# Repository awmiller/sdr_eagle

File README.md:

# sdr_eagle
various designs for different stages of development and manufacturers.

## Clone into the "eagle" directory created by the Eagle CAD installer

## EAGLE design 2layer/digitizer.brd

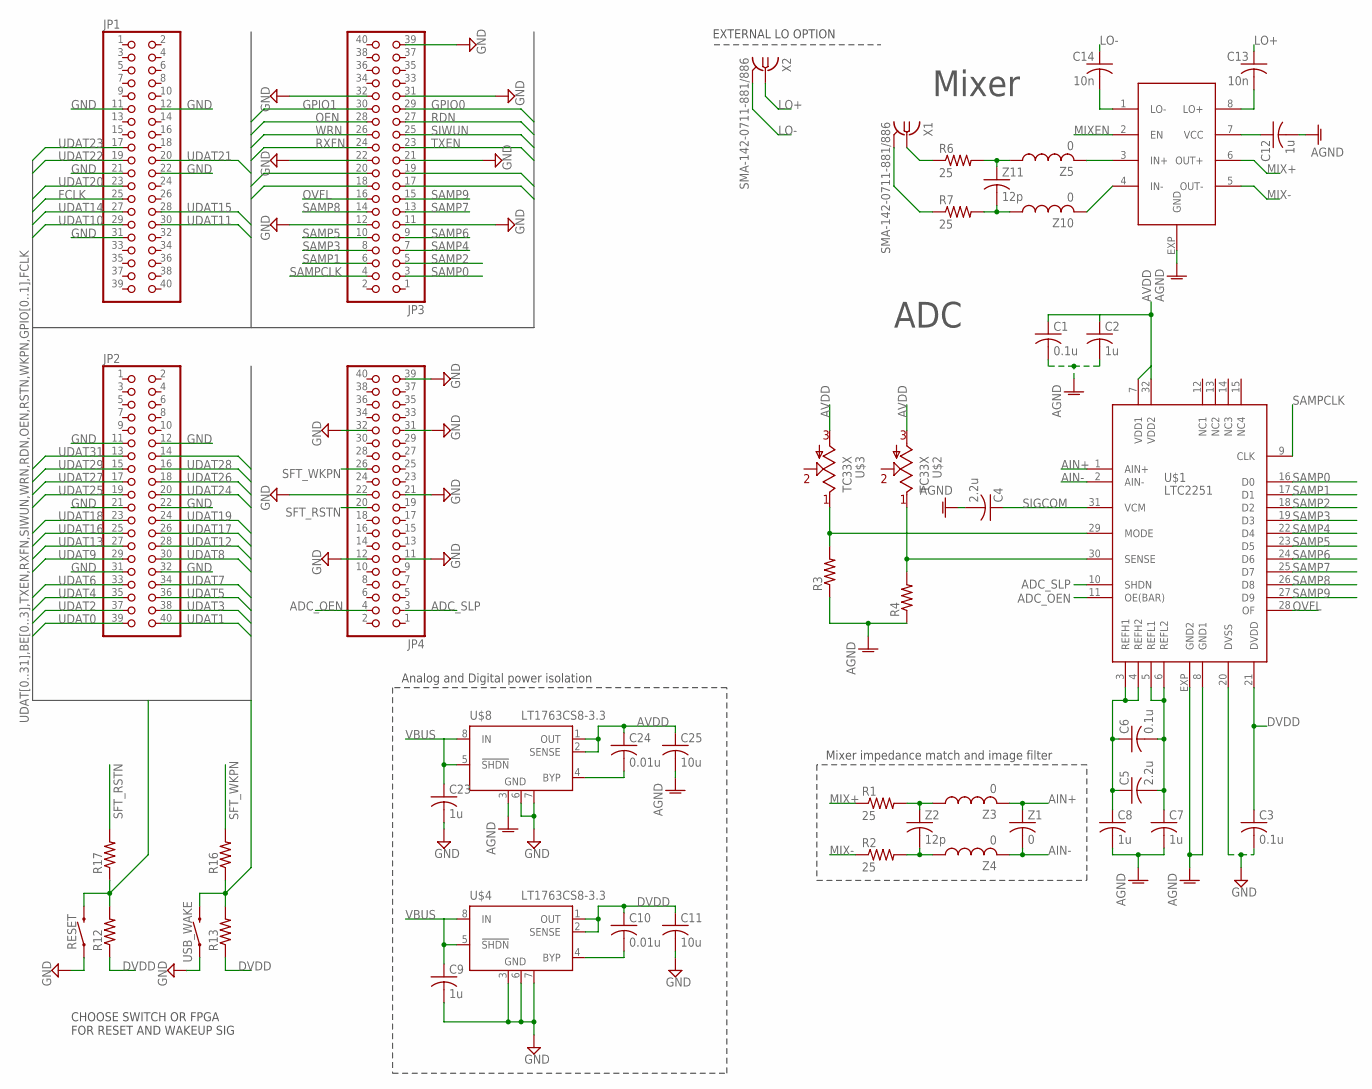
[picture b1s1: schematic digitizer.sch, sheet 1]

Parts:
C1, C3, C6: 0.1u; C0402
C2, C7, C8, C9, C12, C23: 1u; C0402
C4, C5: 2.2u; C0402
C10, C24: 0.01u; C0402
C11, C25: 10u; C0402
C13, C14: 10n; C0402
JP1, JP2, JP3, JP4: PINHD-2X20; 2X20
R1, R2, R6, R7: 25; R0402
R3, R4, R12, R13, R16, R17: R-US_R0402; R0402
RESET: MOMENTARY-SWITCH-SPST-SMD-6.0X3.5MM; TACTILE_SWITCH_SMD_6.0X3.5MM
U$1: LTC2251; HVQFN32
U$2, U$3: TC33X; SC59-POT
U$4, U$8: LT1763CS8-3.3; SOIC8
U$5: LT5560; DFN8-3X3
USB_WAKE: MOMENTARY-SWITCH-SPST-SMD-6.0X3.5MM; TACTILE_SWITCH_SMD_6.0X3.5MM
X1, X2: SMA-142-0711-881/886; J502-ND-142-0711-881/886
Z1: 0; C0402
Z2, Z11: 12p; C0402
Z3, Z4, Z5, Z10: 0; R0402

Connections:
ADC_OEN: JP4.4, U$1.11 (OE(BAR))
ADC_SLP: JP4.3, U$1.10 (SHDN)
AGND: C1.2, C2.2, C4.2, C7.2, C8.2, C12.2, C25.2, R3.1, R4.1, U$1.8 (GND1), U$1.EXP (GND2), U$5.EXP (GND), U$8.3 (GND)
AIN+: U$1.1 (AIN+), Z1.1, Z3.2
AIN-: U$1.2 (AIN-), Z1.2, Z4.2
AVDD: C1.1, C2.1, C24.1, C25.1, U$1.7 (VDD1), U$1.32 (VDD2), U$2.3, U$3.3, U$8.1 (OUT), U$8.2 (SENSE)
BE0: JP3.18; also elsewhere on the board
BE1: JP3.17; also elsewhere on the board
BE2: JP3.20; also elsewhere on the board
BE3: JP3.19; also elsewhere on the board
DVDD: C3.1, C10.1, C11.1, R12.1, R13.1, U$1.21 (DVDD), U$4.1 (OUT), U$4.2 (SENSE); also elsewhere on the board
FCLK: JP1.25; also elsewhere on the board
GND: C3.2, C9.2, C11.2, C23.2, JP1.11, JP1.12, JP1.21, JP1.22, JP1.31, JP2.11, JP2.12, JP2.21, JP2.22, JP2.31, JP2.32, JP3.11, JP3.12, JP3.21, JP3.22, JP3.31, JP3.32, JP3.39, JP4.11, JP4.12, JP4.21, JP4.22, JP4.31, JP4.32, RESET.1, U$1.20 (DVSS), U$4.3 (GND), U$4.6 (GND), U$4.7 (GND), U$8.6 (GND), U$8.7 (GND), USB_WAKE.1; also elsewhere on the board
GPIO0: JP3.29; also elsewhere on the board
GPIO1: JP3.30; also elsewhere on the board
LO+: C13.1, X2.1
LO-: C14.1, X2.G@1 (2), X2.G@2 (2), X2.G@3 (2), X2.G@4 (2)
MIX+: R1.1, U$5.6 (OUT+)
MIX-: R2.1, U$5.5 (OUT-)
MIXEN: U$5.2 (EN)
unnamed: R7.1, X1.G@1 (2), X1.G@2 (2), X1.G@3 (2), X1.G@4 (2)
unnamed: C5.1, C6.1, C8.1, U$1.3 (REFH1), U$1.4 (REFH2)
unnamed: C5.2, C6.2, C7.1, U$1.5 (REFL1), U$1.6 (REFL2)
unnamed: R3.2, U$1.29 (MODE), U$3.1
unnamed: R4.2, U$1.30 (SENSE), U$2.1
unnamed: R1.2, Z2.1, Z3.1
unnamed: R2.2, Z2.2, Z4.1
unnamed: C10.2, U$4.4 (BYP)
unnamed: R6.1, X1.1
unnamed: C24.2, U$8.4 (BYP)
unnamed: C12.1, U$5.7 (VCC)
unnamed: C14.2, U$5.1 (LO-)
unnamed: C13.2, U$5.8 (LO+)
unnamed: R6.2, Z5.1, Z11.1
unnamed: U$5.3 (IN+), Z5.2
unnamed: U$5.4 (IN-), Z10.2
unnamed: R7.2, Z10.1, Z11.2
OEN: JP3.28; also elsewhere on the board
OVFL: JP3.16, U$1.28 (OF)
RDN: JP3.27; also elsewhere on the board
RSTN: R12.2, R17.1, RESET.2; also elsewhere on the board
RXFN: JP3.24; also elsewhere on the board
SAMP0: JP3.3, U$1.16 (D0)
SAMP1: JP3.6, U$1.17 (D1)
SAMP2: JP3.5, U$1.18 (D2)
SAMP3: JP3.8, U$1.19 (D3)
SAMP4: JP3.7, U$1.22 (D4)
SAMP5: JP3.10, U$1.23 (D5)
SAMP6: JP3.9, U$1.24 (D6)
SAMP7: JP3.13, U$1.25 (D7)
SAMP8: JP3.14, U$1.26 (D8)
SAMP9: JP3.15, U$1.27 (D9)
SAMPCLK: JP3.4, U$1.9 (CLK)
SFT_RSTN: JP4.20, R17.2
SFT_WKPN: JP4.26, R16.2
SIGCOM: C4.1, U$1.31 (VCM)
SIWUN: JP3.25; also elsewhere on the board
TXEN: JP3.23; also elsewhere on the board
UDAT0: JP2.39; also elsewhere on the board
UDAT1: JP2.40; also elsewhere on the board
UDAT2: JP2.37; also elsewhere on the board
UDAT3: JP2.38; also elsewhere on the board
UDAT4: JP2.35; also elsewhere on the board
UDAT5: JP2.36; also elsewhere on the board
UDAT6: JP2.33; also elsewhere on the board
UDAT7: JP2.34; also elsewhere on the board
UDAT8: JP2.30; also elsewhere on the board
UDAT9: JP2.29; also elsewhere on the board
UDAT10: JP1.29; also elsewhere on the board
UDAT11: JP1.30; also elsewhere on the board
UDAT12: JP2.28; also elsewhere on the board
UDAT13: JP2.27; also elsewhere on the board
UDAT14: JP1.27; also elsewhere on the board
UDAT15: JP1.28; also elsewhere on the board
UDAT16: JP2.25; also elsewhere on the board
UDAT17: JP2.26; also elsewhere on the board
UDAT18: JP2.23; also elsewhere on the board
UDAT19: JP2.24; also elsewhere on the board
UDAT20: JP1.23; also elsewhere on the board
UDAT21: JP1.20; also elsewhere on the board
UDAT22: JP1.19; also elsewhere on the board
UDAT23: JP1.17; also elsewhere on the board
UDAT24: JP2.20; also elsewhere on the board
UDAT25: JP2.19; also elsewhere on the board
UDAT26: JP2.18; also elsewhere on the board
UDAT27: JP2.17; also elsewhere on the board
UDAT28: JP2.16; also elsewhere on the board
UDAT29: JP2.15; also elsewhere on the board
UDAT30: JP2.14; also elsewhere on the board
UDAT31: JP2.13; also elsewhere on the board
VBUS: C9.1, C23.1, U$4.5 (!SHDN), U$4.8 (IN), U$8.5 (!SHDN), U$8.8 (IN); also elsewhere on the board
WKPN: R13.2, R16.1, USB_WAKE.2; also elsewhere on the board
WRN: JP3.26; also elsewhere on the board

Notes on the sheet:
Mixer impedance match and image filter
Analog and Digital power isolation
Mixer
ADC
EXTERNAL LO OPTION
CHOOSE SWITCH OR FPGA FOR RESET AND WAKEUP SIG

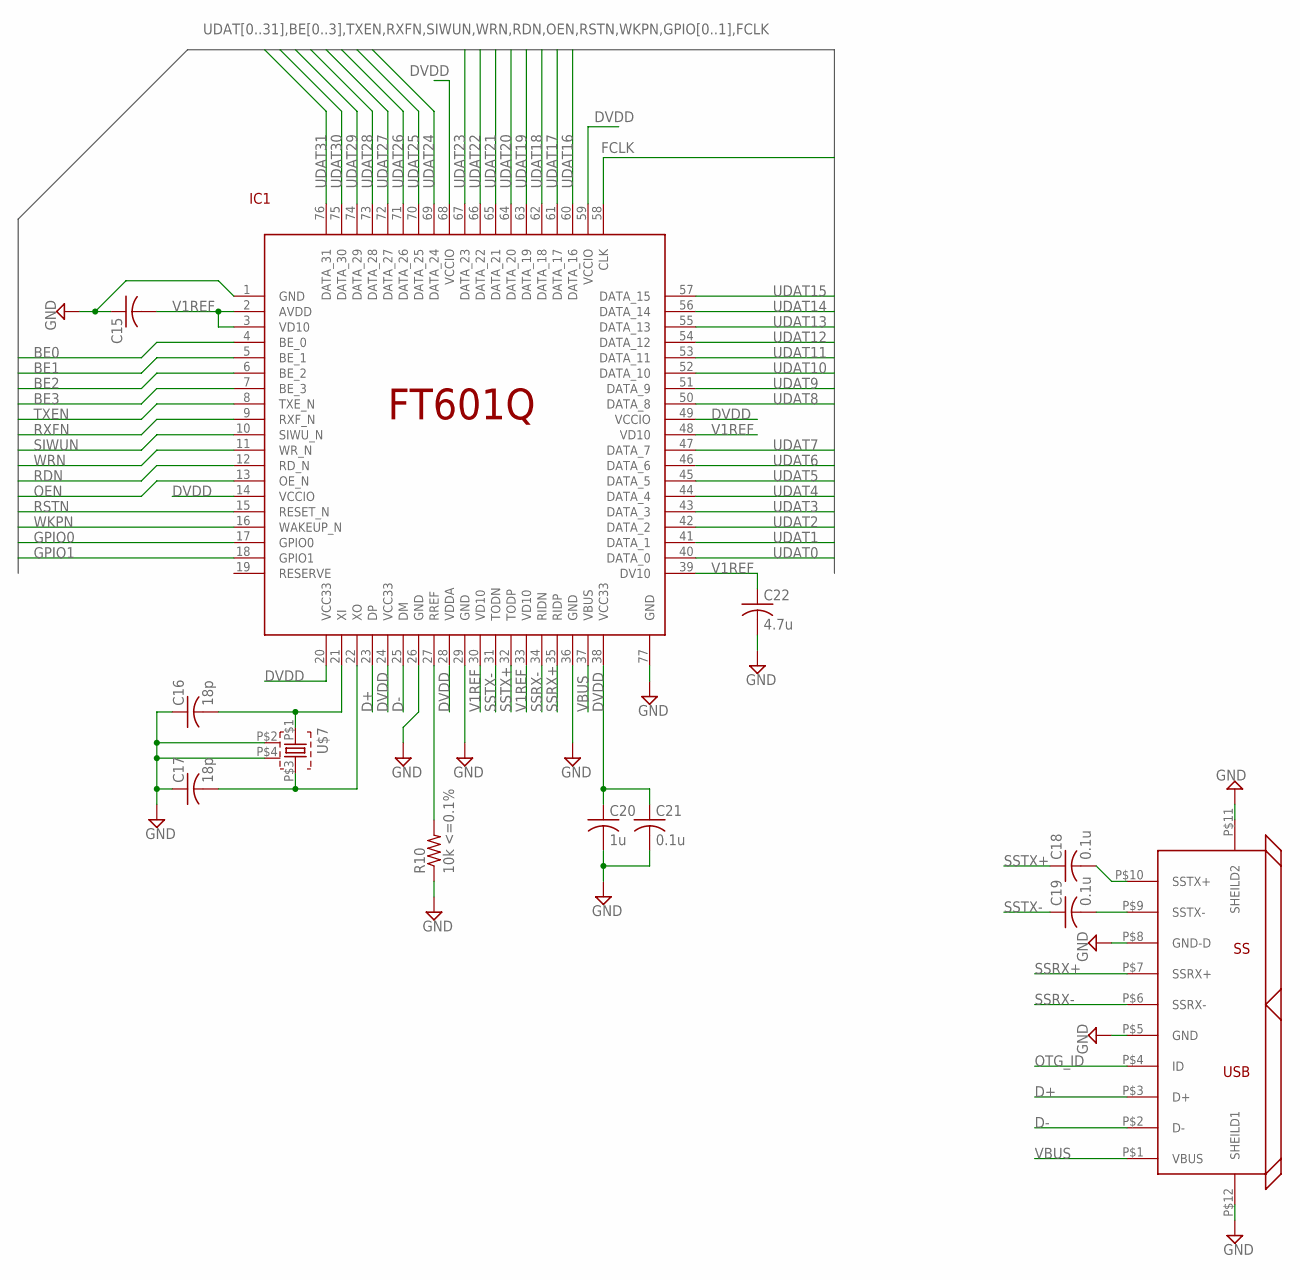
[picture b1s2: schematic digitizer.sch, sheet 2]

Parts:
C15: C-USC0402; C0402
C16, C17: 18p; C0402
C18, C19, C21: 0.1u; C0402
C20: 1u; C0402
C22: 4.7u; C0402
IC1: FT601QQFN76; QFN76
R10: 10k <=0.1%; R0402
U$6: USB3.0; USB-MICROB-3.0
U$7: CX3225SB_UKY1C-H1-16357-0045; UKY1C-H1-16357-0045

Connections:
BE0: IC1.4 (BE_0); also elsewhere on the board
BE1: IC1.5 (BE_1); also elsewhere on the board
BE2: IC1.6 (BE_2); also elsewhere on the board
BE3: IC1.7 (BE_3); also elsewhere on the board
D+: IC1.23 (DP), U$6.P$3 (D+)
D-: IC1.25 (DM), U$6.P$2 (D-)
DVDD: C20.1, C21.1, IC1.14 (VCCIO), IC1.20 (VCC33), IC1.24 (VCC33), IC1.28 (VDDA), IC1.38 (VCC33), IC1.49 (VCCIO), IC1.59 (VCCIO), IC1.68 (VCCIO); also elsewhere on the board
FCLK: IC1.58 (CLK); also elsewhere on the board
GND: C15.1, C16.1, C17.1, C20.2, C21.2, C22.2, IC1.1 (GND), IC1.26 (GND), IC1.29 (GND), IC1.36 (GND), IC1.77 (GND), R10.1, U$6.P$5 (GND), U$6.P$8 (GND-D), U$6.P$11 (SHEILD2), U$6.P$12 (SHEILD1), U$7.P$2 (2), U$7.P$4 (4); also elsewhere on the board
GPIO0: IC1.17 (GPIO0); also elsewhere on the board
GPIO1: IC1.18 (GPIO1); also elsewhere on the board
unnamed: C16.2, IC1.21 (XI), U$7.P$1 (1)
unnamed: C17.2, IC1.22 (XO), U$7.P$3 (3)
unnamed: IC1.27 (RREF), R10.2
unnamed: C18.2, U$6.P$10 (SSTX+)
unnamed: C19.2, U$6.P$9 (SSTX-)
OEN: IC1.13 (OE_N); also elsewhere on the board
OTG_ID: U$6.P$4 (ID)
RDN: IC1.12 (RD_N); also elsewhere on the board
RSTN: IC1.15 (RESET_N); also elsewhere on the board
RXFN: IC1.9 (RXF_N); also elsewhere on the board
SIWUN: IC1.10 (SIWU_N); also elsewhere on the board
SSRX+: IC1.35 (RIDP), U$6.P$7 (SSRX+)
SSRX-: IC1.34 (RIDN), U$6.P$6 (SSRX-)
SSTX+: C18.1, IC1.32 (TODP)
SSTX-: C19.1, IC1.31 (TODN)
TXEN: IC1.8 (TXE_N); also elsewhere on the board
UDAT0: IC1.40 (DATA_0); also elsewhere on the board
UDAT1: IC1.41 (DATA_1); also elsewhere on the board
UDAT2: IC1.42 (DATA_2); also elsewhere on the board
UDAT3: IC1.43 (DATA_3); also elsewhere on the board
UDAT4: IC1.44 (DATA_4); also elsewhere on the board
UDAT5: IC1.45 (DATA_5); also elsewhere on the board
UDAT6: IC1.46 (DATA_6); also elsewhere on the board
UDAT7: IC1.47 (DATA_7); also elsewhere on the board
UDAT8: IC1.50 (DATA_8); also elsewhere on the board
UDAT9: IC1.51 (DATA_9); also elsewhere on the board
UDAT10: IC1.52 (DATA_10); also elsewhere on the board
UDAT11: IC1.53 (DATA_11); also elsewhere on the board
UDAT12: IC1.54 (DATA_12); also elsewhere on the board
UDAT13: IC1.55 (DATA_13); also elsewhere on the board
UDAT14: IC1.56 (DATA_14); also elsewhere on the board
UDAT15: IC1.57 (DATA_15); also elsewhere on the board
UDAT16: IC1.60 (DATA_16); also elsewhere on the board
UDAT17: IC1.61 (DATA_17); also elsewhere on the board
UDAT18: IC1.62 (DATA_18); also elsewhere on the board
UDAT19: IC1.63 (DATA_19); also elsewhere on the board
UDAT20: IC1.64 (DATA_20); also elsewhere on the board
UDAT21: IC1.65 (DATA_21); also elsewhere on the board
UDAT22: IC1.66 (DATA_22); also elsewhere on the board
UDAT23: IC1.67 (DATA_23); also elsewhere on the board
UDAT24: IC1.69 (DATA_24); also elsewhere on the board
UDAT25: IC1.70 (DATA_25); also elsewhere on the board
UDAT26: IC1.71 (DATA_26); also elsewhere on the board
UDAT27: IC1.72 (DATA_27); also elsewhere on the board
UDAT28: IC1.73 (DATA_28); also elsewhere on the board
UDAT29: IC1.74 (DATA_29); also elsewhere on the board
UDAT30: IC1.75 (DATA_30); also elsewhere on the board
UDAT31: IC1.76 (DATA_31); also elsewhere on the board
V1REF: C15.2, C22.1, IC1.2 (AVDD), IC1.3 (VD10), IC1.30 (VD10), IC1.33 (VD10), IC1.39 (DV10), IC1.48 (VD10)
VBUS: IC1.37 (VBUS), U$6.P$1 (VBUS); also elsewhere on the board
WKPN: IC1.16 (WAKEUP_N); also elsewhere on the board
WRN: IC1.11 (WR_N); also elsewhere on the board

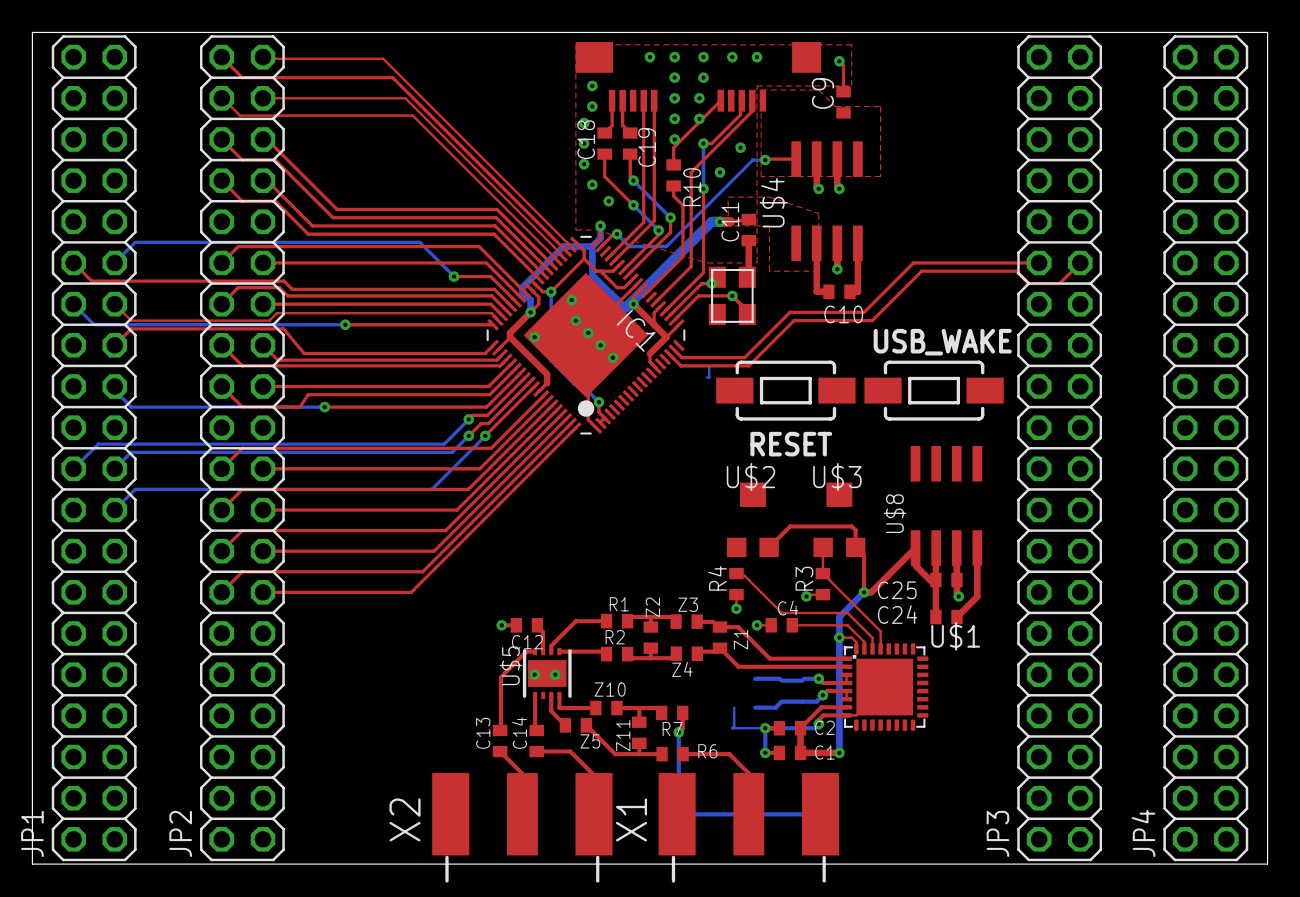
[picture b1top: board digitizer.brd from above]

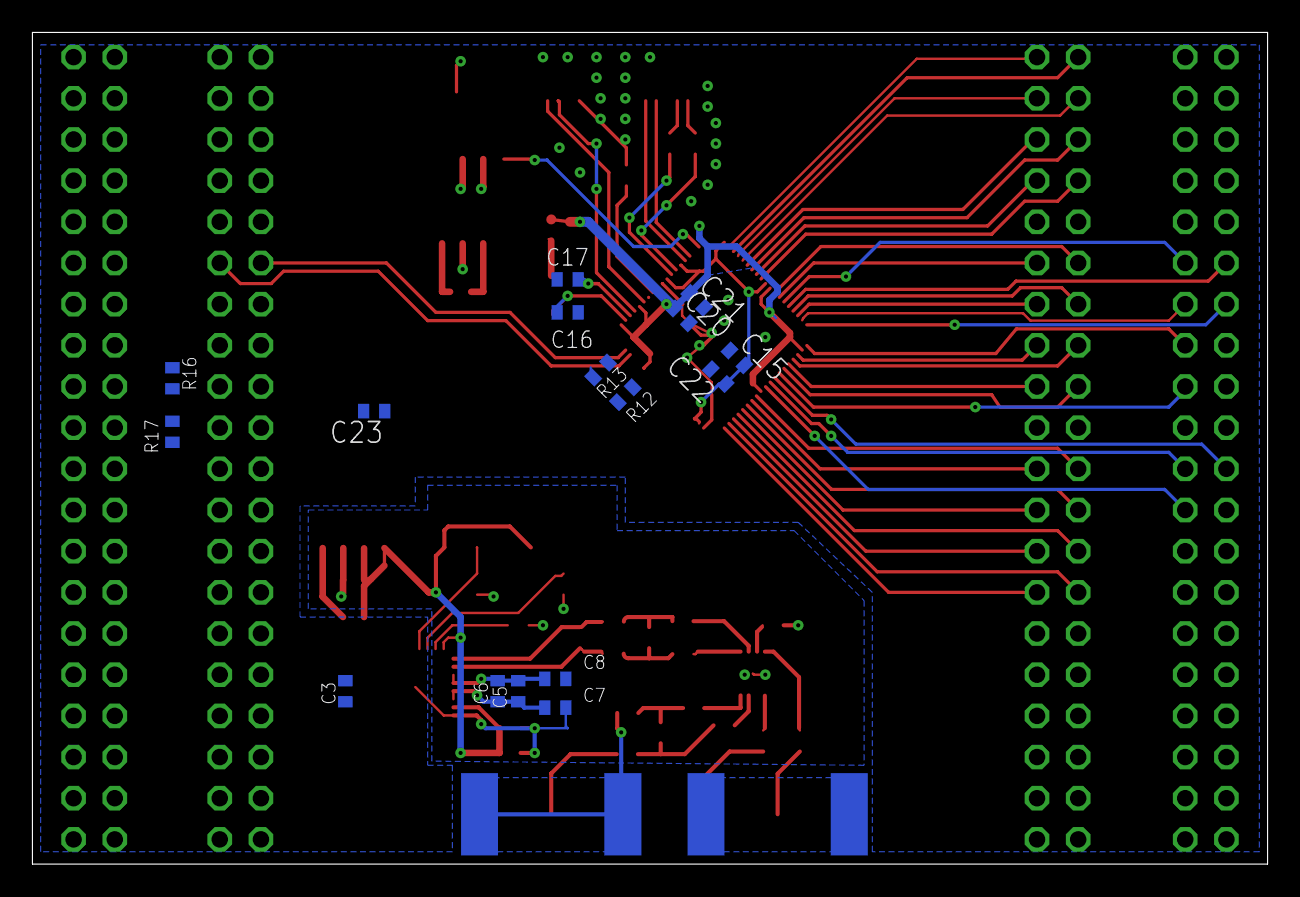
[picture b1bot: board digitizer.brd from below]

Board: 2 copper layers, 76.2 x 51.3 mm, 60 parts (16 on the bottom side), 104 nets.

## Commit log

2017-02-27 first pass digitizer board
2017-02-28 fixed readme
2017-02-28 added some passives to ADC
2017-03-02 addded reg
2017-03-04 added some layout
2017-03-05 started layout
2017-03-06 started layout2
2017-03-14 okanwd;ojbawol
2017-04-03 starting final layout
2017-04-03 okawndpam
2017-04-03 moved guts to center to make more of a sheild-like adaptor to mate with MACH
2017-04-04 started meandering fifo bus
2017-04-05 fixed header positions to match mach
2017-04-05 almost done allocating wires
2017-04-05 added dual regulator solution for power isolation
2017-04-06 added pours
2017-04-07 autorouter sucks, trying manual
2017-04-07 routing routing routing....

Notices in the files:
parts and their libraries:
SparkFun-Switches: Licensing: Creative Commons ShareAlike 4.0 International - https://creativecommons.org/licenses/by-sa/4.0
